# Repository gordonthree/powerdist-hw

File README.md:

# powerdist-hw
Power distribution board to combine multiple batteries with multiple power supplies

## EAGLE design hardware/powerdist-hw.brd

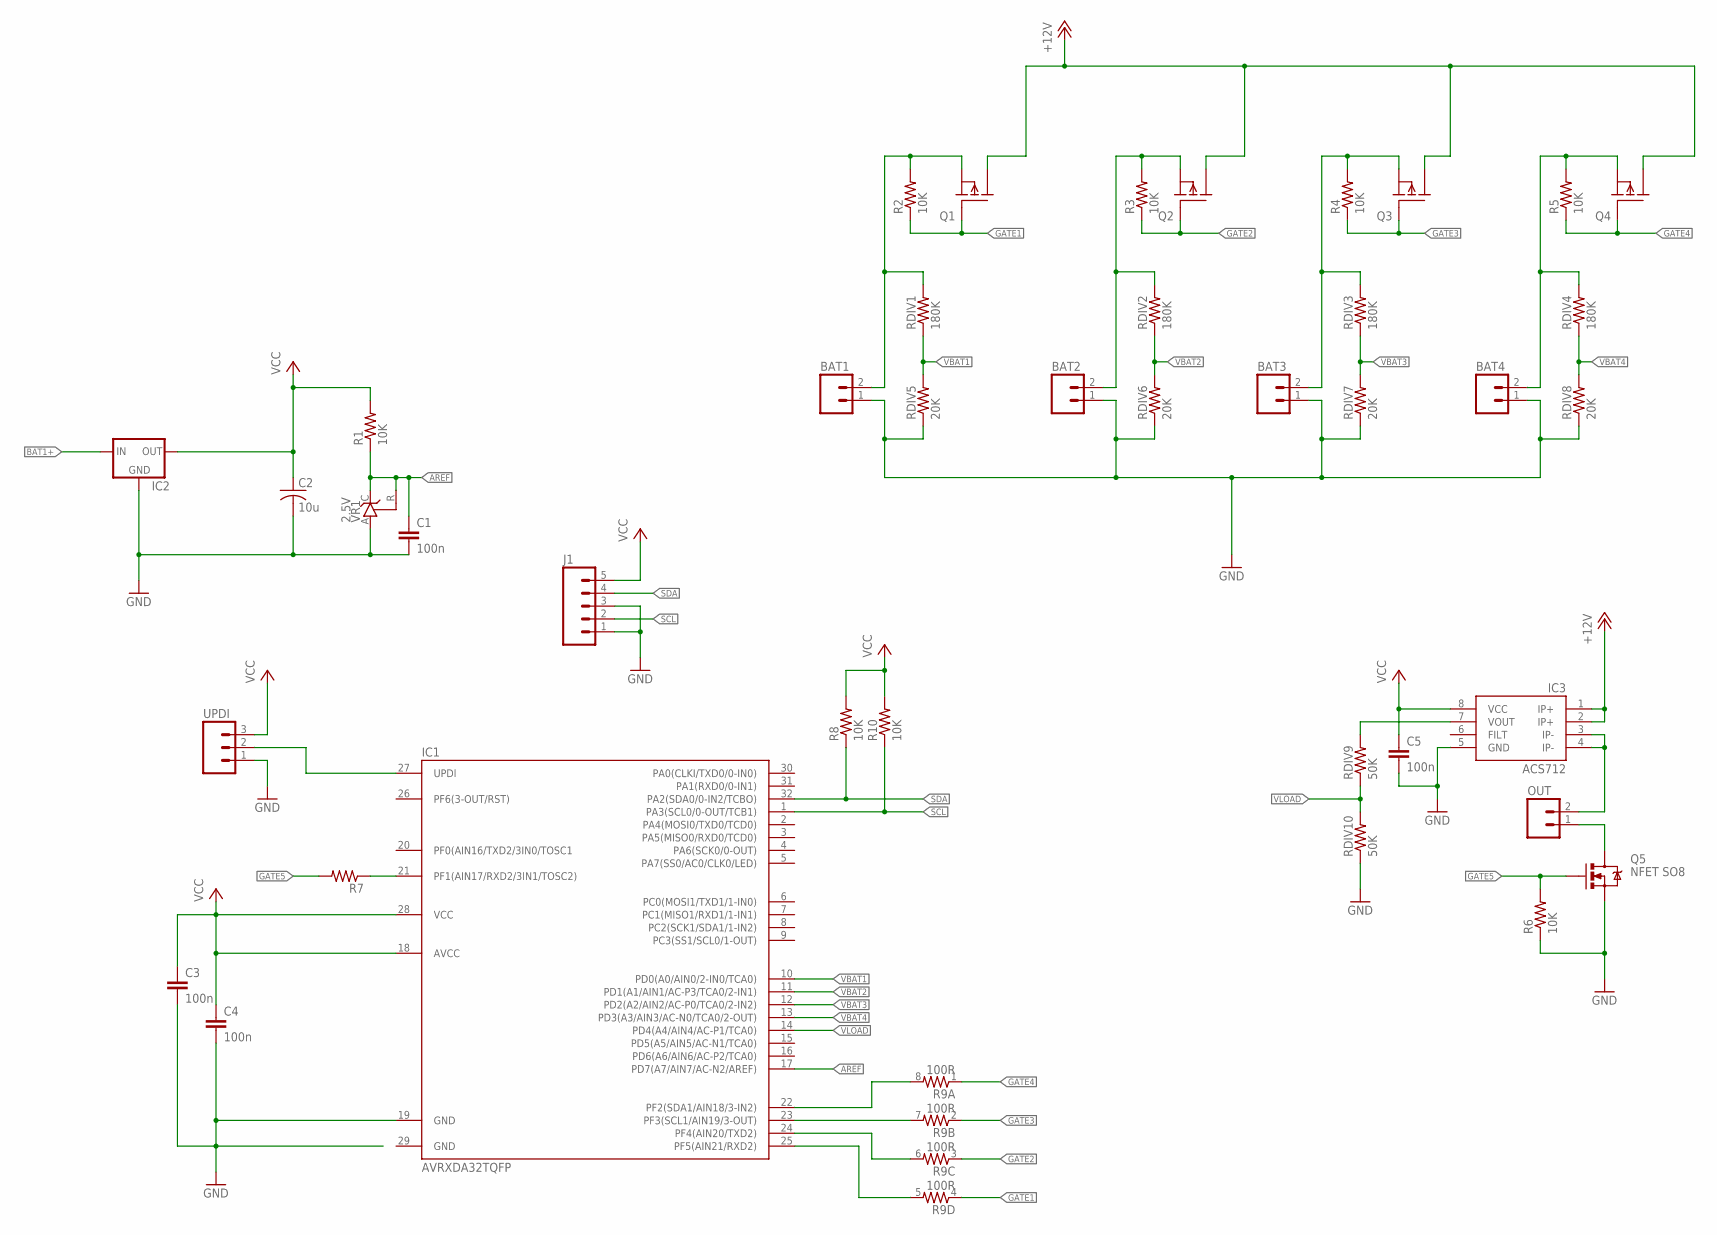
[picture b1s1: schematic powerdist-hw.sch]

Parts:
BAT1, BAT2, BAT3, BAT4: M02LOCK_LONGPADS; 1X02_LOCK_LONGPADS
C1, C3, C4, C5: 100n; C0603
C2: 10u; C0805
IC1: AVRXDA32TQFP; TQFP32-08
IC2: 78XXS
IC3: ACS712; SO08
J1: M05JST; JST-5-PTH
OUT: M02LOCK_LONGPADS; 1X02_LOCK_LONGPADS
Q1, Q2, Q3, Q4: PFETSO8; SO-08
Q5: NFET SO8; SO08
R1, R2, R3, R4, R5, R6, R8, R10: 10K; R0603
R7: R-US_R0603; R0603
R9: 100R; 0603-ARV
RDIV1, RDIV2, RDIV3, RDIV4: 180K; 0805
RDIV5, RDIV6, RDIV7, RDIV8: 20K; 0805
RDIV9, RDIV10: 50K; 0805
UPDI: M03PTH; 1X03
VR1: 2.5V; TO92-CLP

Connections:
+12V: IC3.1 (IP+), IC3.2 (IP+), Q1.5 (D), Q1.6 (D), Q1.7 (D), Q1.8 (D), Q2.5 (D), Q2.6 (D), Q2.7 (D), Q2.8 (D), Q3.5 (D), Q3.6 (D), Q3.7 (D), Q3.8 (D), Q4.5 (D), Q4.6 (D), Q4.7 (D), Q4.8 (D)
AREF: C1.1, IC1.17 (PD7(A7/AIN7/AC-N2/AREF)), R1.1, VR1.C, VR1.R
BAT1+: BAT1.2, IC2.IN, Q1.1 (S), Q1.2 (S), Q1.3 (S), R2.2, RDIV1.2
BAT2+: BAT2.2, Q2.1 (S), Q2.2 (S), Q2.3 (S), R3.2, RDIV2.2
BAT3+: BAT3.2, Q3.1 (S), Q3.2 (S), Q3.3 (S), R4.2, RDIV3.2
BAT4+: BAT4.2, Q4.1 (S), Q4.2 (S), Q4.3 (S), R5.2, RDIV4.2
GATE1: Q1.4 (G), R2.1, R9.4 (1)
GATE1`: IC1.25 (PF5(AIN21/RXD2)), R9.5 (2)
GATE2: Q2.4 (G), R3.1, R9.3 (1)
GATE3: Q3.4 (G), R4.1, R9.2 (1)
GATE4: Q4.4 (G), R5.1, R9.1
GATE5: Q5.4 (G), R6.2, R7.2
GATE5`: IC1.21 (PF1(AIN17/RXD2/3IN1/TOSC2)), R7.1
GND: BAT1.1, BAT2.1, BAT3.1, BAT4.1, C1.2, C2.2, C3.2, C4.2, C5.2, IC1.19 (GND), IC1.29 (GND), IC2.GND, IC3.5 (GND), J1.1, J1.3, Q5.1 (S), Q5.2 (S), Q5.3 (S), R6.1, RDIV5.1, RDIV6.1, RDIV7.1, RDIV8.1, RDIV10.1, UPDI.1, VR1.A
unnamed: IC3.7 (VOUT), RDIV9.2
unnamed: IC1.27 (UPDI), UPDI.2
unnamed: IC1.22 (PF2(SDA1/AIN18/3-IN2)), R9.8 (2)
unnamed: IC1.23 (PF3(SCL1/AIN19/3-OUT)), R9.7 (2)
unnamed: IC1.24 (PF4(AIN20/TXD2)), R9.6 (2)
OUT+: IC3.3 (IP-), IC3.4 (IP-), OUT.2
OUT-: OUT.1, Q5.5 (D), Q5.6 (D), Q5.7 (D), Q5.8 (D)
SCL: IC1.1 (PA3(SCL0/0-OUT/TCB1)), J1.2, R10.1
SDA: IC1.32 (PA2(SDA0/0-IN2/TCBO)), J1.4, R8.1
VBAT1: IC1.10 (PD0(A0/AIN0/2-IN0/TCA0)), RDIV1.1, RDIV5.2
VBAT2: IC1.11 (PD1(A1/AIN1/AC-P3/TCA0/2-IN1)), RDIV2.1, RDIV6.2
VBAT3: IC1.12 (PD2(A2/AIN2/AC-P0/TCA0/2-IN2)), RDIV3.1, RDIV7.2
VBAT4: IC1.13 (PD3(A3/AIN3/AC-N0/TCA0/2-OUT)), RDIV4.1, RDIV8.2
VCC: C2.1, C3.1, C4.1, C5.1, IC1.18 (AVCC), IC1.28 (VCC), IC2.OUT, IC3.8 (VCC), J1.5, R1.2, R8.2, R10.2, UPDI.3
VLOAD: IC1.14 (PD4(A4/AIN4/AC-P1/TCA0)), RDIV9.1, RDIV10.2

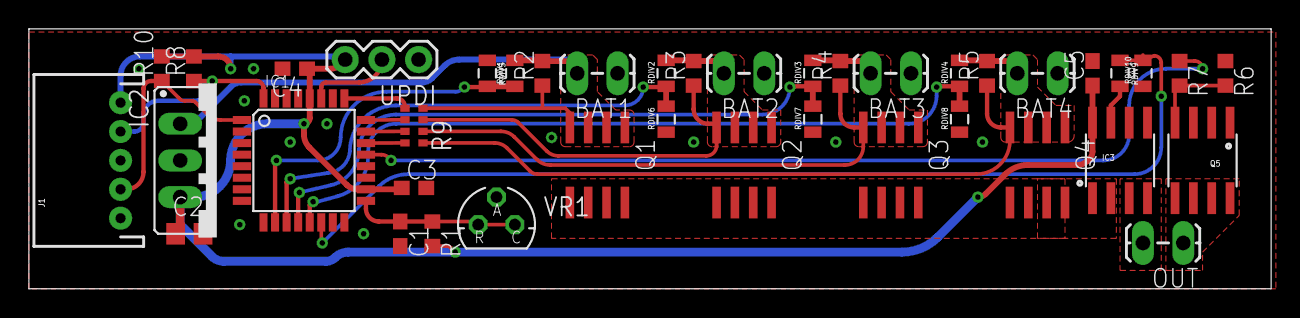
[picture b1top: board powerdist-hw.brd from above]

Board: 2 copper layers, 86.0 x 18.0 mm, 41 parts (0 on the bottom side), 29 nets.

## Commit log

2022-08-24 rough draft
2022-08-25 lots of progress
2022-08-25 layout complete

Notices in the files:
parts and their libraries:
SparkFun-Resistors: Licensing: Creative Commons ShareAlike 4.0 International - https://creativecommons.org/licenses/by-sa/4.0
